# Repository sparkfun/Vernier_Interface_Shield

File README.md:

SparkFun Vernier Interface Shield Arduino Library
=================================================

[*SparkFun Vernier Interface Shield*](https://www.sparkfun.com/products/12858)

Repository Contents
-------------------

* **/src** - Source files for the library (.cpp, .h).
* **library.properties** - General library properties for the Arduino package manager. 
**Note**: For example sketches, please check the Vernier repository [here](https://github.com/VernierSoftwareTechnology/arduino).

Documentation
--------------
* **[Installing an Arduino Library Guide](https://learn.sparkfun.com/tutorials/installing-an-arduino-library)** - Basic information on how to install an Arduino library.
* **[Product Repository](https://github.com/sparkfun/Vernier_Interface_Shield)** - Main repository (including hardware files).
* **[Hookup Guide](https://learn.sparkfun.com/tutorials/vernier-shield-hookup-guide)** - Basic hookup guide for the SparkFun Vernier Interface Shield.

Products that use this Library 
---------------------------------

* [DEV-12858](https://www.sparkfun.com/products/12858)- SparkFun Vernier Interface Shield

License Information
-------------------

This product is _**open source**_! 

The **code** is beerware; if you see me (or any other SparkFun employee) at the local, and you've found our code helpful, please buy us a round!

Please use, reuse, and modify these files as you see fit. Please maintain attribution to SparkFun Electronics and release anything derivative under the same license.

Distributed as-is; no warranty is given.

- Your friends at SparkFun.

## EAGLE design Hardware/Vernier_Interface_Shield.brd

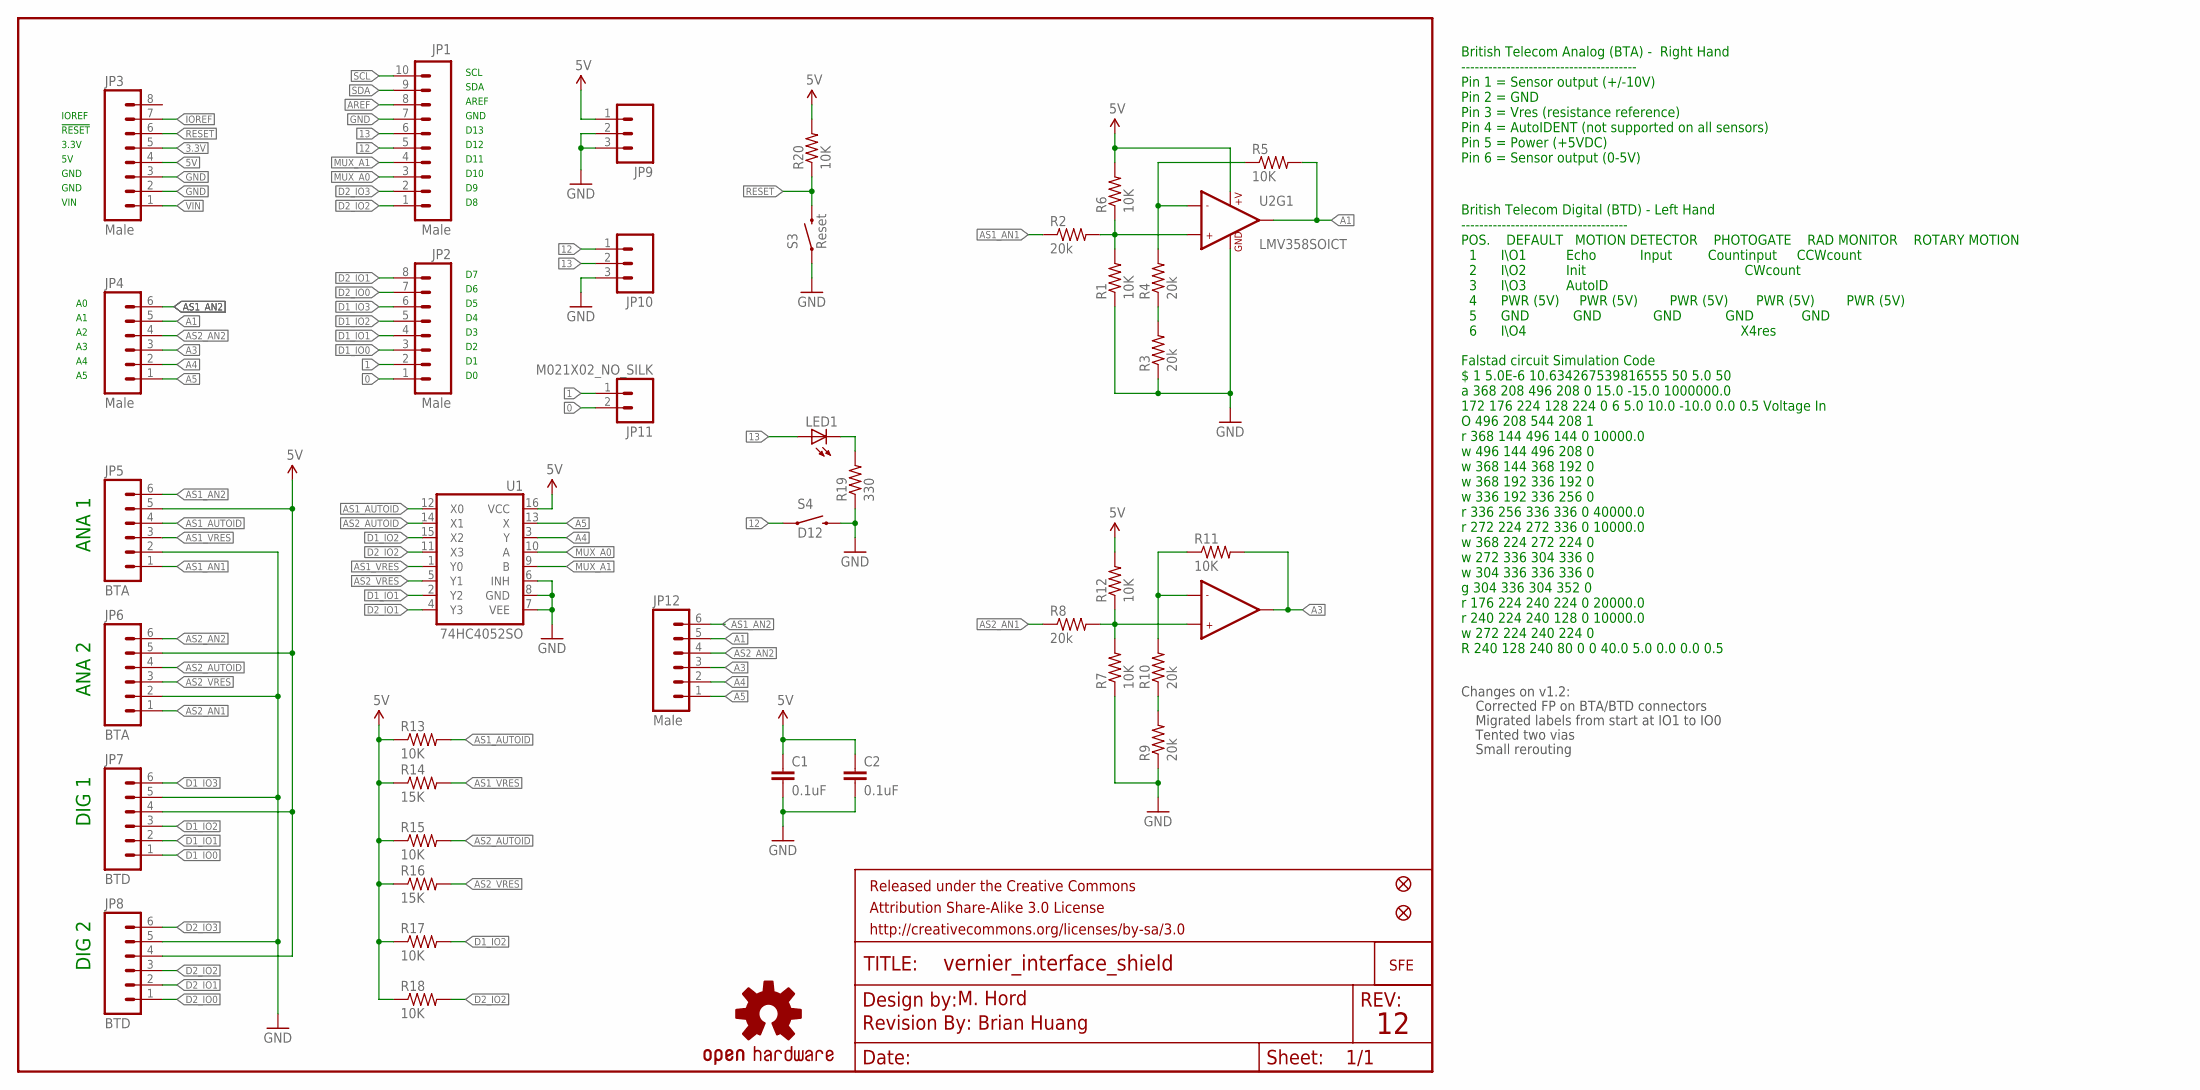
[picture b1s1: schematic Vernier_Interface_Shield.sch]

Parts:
C1, C2: 0.1uF; 0603-CAP
FID1, FID2: FIDUCIAL1X2; FIDUCIAL-1X2
FRAME1: FRAME-LETTER; CREATIVE_COMMONS
JP1: Male; 1X10_SMD_MALE
JP2, JP3: Male; 1X08_SMD_MALE
JP4: Male; 1X06_SMD_MALE
JP5, JP6: BTA
JP7, JP8: BTD
JP9, JP10: M031X03_NO_SILK; 1X03_NO_SILK
JP11: M021X02_NO_SILK; 1X02_NO_SILK
JP12: Male; 1X06
LED1: LED5MM
LOGO2: OSHW-LOGOS; OSHW-LOGO-S
LOGO_1: LOGO-SFESK; SFE-LOGO-FLAME
R1, R5, R6, R7, R11, R12, R13, R15, R17, R18, R20: 10K; 0603-RES
R2, R3, R4, R8, R9, R10: 20k; 0603-RES
R14, R16: 15K; 0603-RES
R19: 330; 0603-RES
S3: Reset; TACTILE-PTH
S4: D12; TACTILE-PTH
U1: 74HC4052SO; SO16
U2: LMV358SOICT; SO08-TIGHT
U$1: REVISION

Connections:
0: JP2.1, JP11.2
1: JP2.2, JP11.1
3.3V: JP3.5
5V: C1.1, C2.1, JP3.4, JP5.5, JP6.5, JP7.4, JP8.4, JP9.1, R6.2, R12.2, R13.1, R14.1, R15.1, R16.1, R17.1, R18.1, R20.2, U1.16 (VCC), U2.8 (+V)
12: JP1.5, JP10.1, S4.1
13: JP1.6, JP10.2, LED1.A
A1: JP4.5, JP12.5, R5.2, U2.1 (OUT1)
A3: JP4.3, JP12.3, R11.2, U2.7 (OUT2)
A4: JP4.2, JP12.2, U1.3 (Y)
A5: JP4.1, JP12.1, U1.13 (X)
AREF: JP1.8
AS1_AN1: JP5.1, R2.1
AS1_AN2: JP4.6, JP5.6, JP12.6
AS1_AUTOID: JP5.4, R13.2, U1.12 (X0)
AS1_VRES: JP5.3, R14.2, U1.1 (Y0)
AS2_AN1: JP6.1, R8.1
AS2_AN2: JP4.4, JP6.6, JP12.4
AS2_AUTOID: JP6.4, R15.2, U1.14 (X1)
AS2_VRES: JP6.3, R16.2, U1.5 (Y1)
D1_IO0: JP2.3, JP7.1
D1_IO1: JP2.4, JP7.2, U1.2 (Y2)
D1_IO2: JP2.5, JP7.3, R17.2, U1.15 (X2)
D1_IO3: JP2.6, JP7.6
D2_IO0: JP2.7, JP8.1
D2_IO1: JP2.8, JP8.2, U1.4 (Y3)
D2_IO2: JP1.1, JP8.3, R18.2, U1.11 (X3)
D2_IO3: JP1.2, JP8.6
GND: C1.2, C2.2, JP1.7, JP3.2, JP3.3, JP5.2, JP6.2, JP7.5, JP8.5, JP9.2, JP9.3, JP10.3, R1.1, R3.1, R7.1, R9.1, R19.1, S3.1, S4.3 (2), U1.6 (INH), U1.7 (VEE), U1.8 (GND), U2.4 (GND)
IOREF: JP3.7
MUX_A0: JP1.3, U1.10 (A)
MUX_A1: JP1.4, U1.9 (B)
unnamed: R1.2, R2.2, R6.1, U2.3 (+IN1)
unnamed: R3.2, R4.1
unnamed: R4.2, R5.1, U2.2 (-IN1)
unnamed: R9.2, R10.1
unnamed: R7.2, R8.2, R12.1, U2.5 (+IN2)
unnamed: R10.2, R11.1, U2.6 (-IN2)
unnamed: LED1.K (C), R19.2
RESET: JP3.6, R20.1, S3.3 (2)
SCL: JP1.10
SDA: JP1.9
VIN: JP3.1

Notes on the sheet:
SCL
SDA
AREF
GND
D13
D12
D11
D10
VIN
3.3V
!RESET
IOREF
ANA 1
ANA 2
DIG 1
DIG 2
M. Hord
British Telecom Analog (BTA) - Right Hand --------------------------------------- Pin 1 = Sensor output (+/-10V) Pin 2 = GND Pin 3 = Vres (resistance reference) Pin 4 = AutoIDENT (not supported on all sensors) Pin 5 = Power (+5VDC) Pin 6 = Sensor output (0-5V)
British Telecom Digital (BTD) - Left Hand ------------------------------------- POS. DEFAULT MOTION DETECTOR PHOTOGATE RAD MONITOR ROTARY MOTION 1 I\\O1 Echo Input Countinput CCWcount 2 I\\O2 Init CWcount 3 I\\O3 AutoID 4 PWR (5V) PWR (5V) PWR (5V) PWR (5V) PWR (5V) 5 GND GND GND GND GND 6 I\\O4 X4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
Falstad circuit Simulation Code $ 1 5.0E-6 10.634267539816555 50 5.0 50 a 368 208 496 208 0 15.0 -15.0 1000000.0 172 176 224 128 224 0 6 5.0 10.0 -10.0 0.0 0.5 Voltage In O 496 208 544 208 1 r 368 144 496 144 0 10000.0 w 496 144 496 208 0 w 368 144 368 192 0 w 368 192 336 192 0 w 336 192 336 256 0 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
Changes on v1.2:
Corrected FP on BTA/BTD connectors
Migrated labels from start at IO1 to IO0
Tented two vias
Small rerouting
Brian Huang

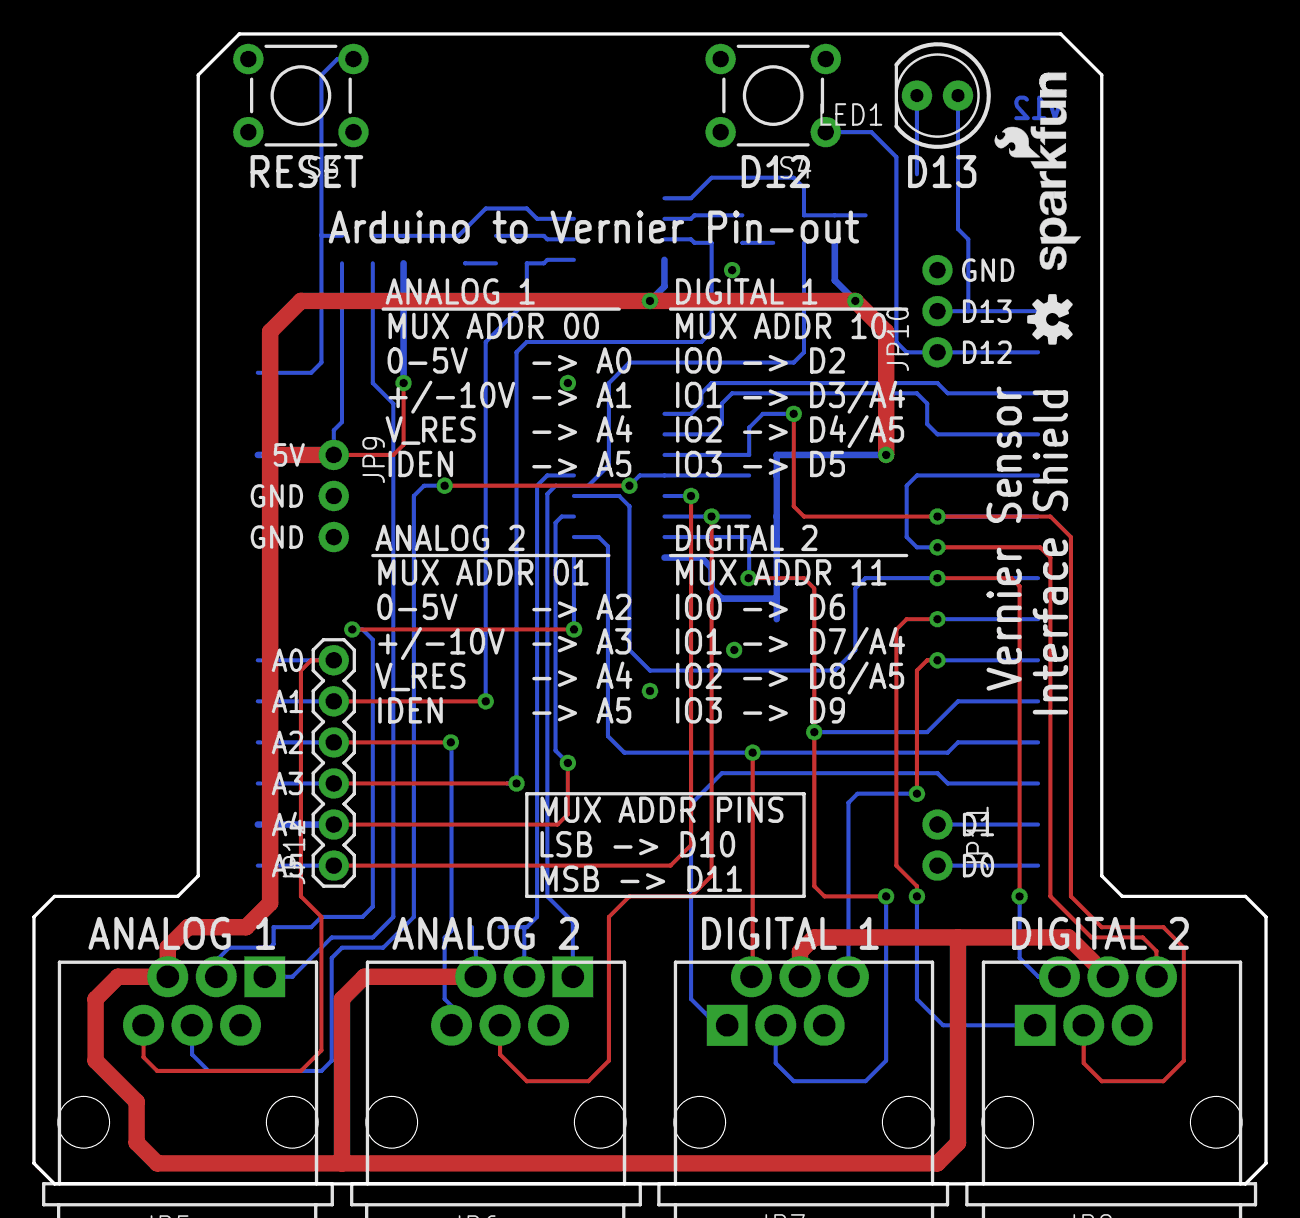
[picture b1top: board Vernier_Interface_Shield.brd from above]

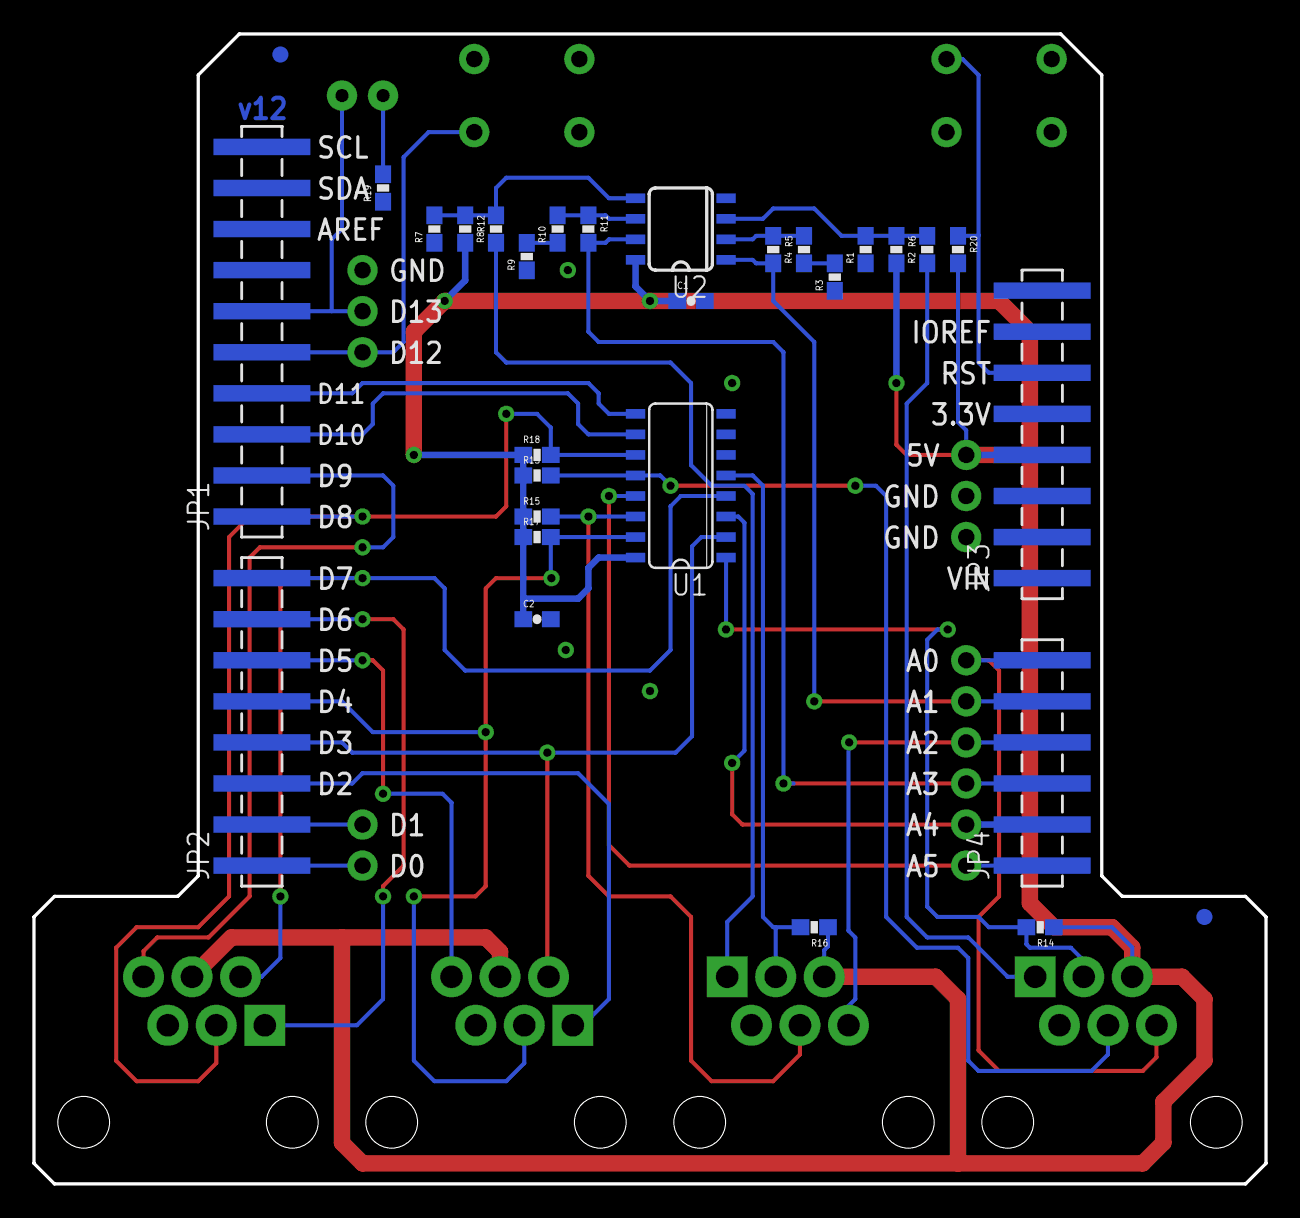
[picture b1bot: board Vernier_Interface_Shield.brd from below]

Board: 2 copper layers, 76.2 x 71.1 mm, 46 parts (30 on the bottom side), 36 nets.

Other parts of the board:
LOGO_3: LOGO-SFENW2; SFE-NEW-WEB

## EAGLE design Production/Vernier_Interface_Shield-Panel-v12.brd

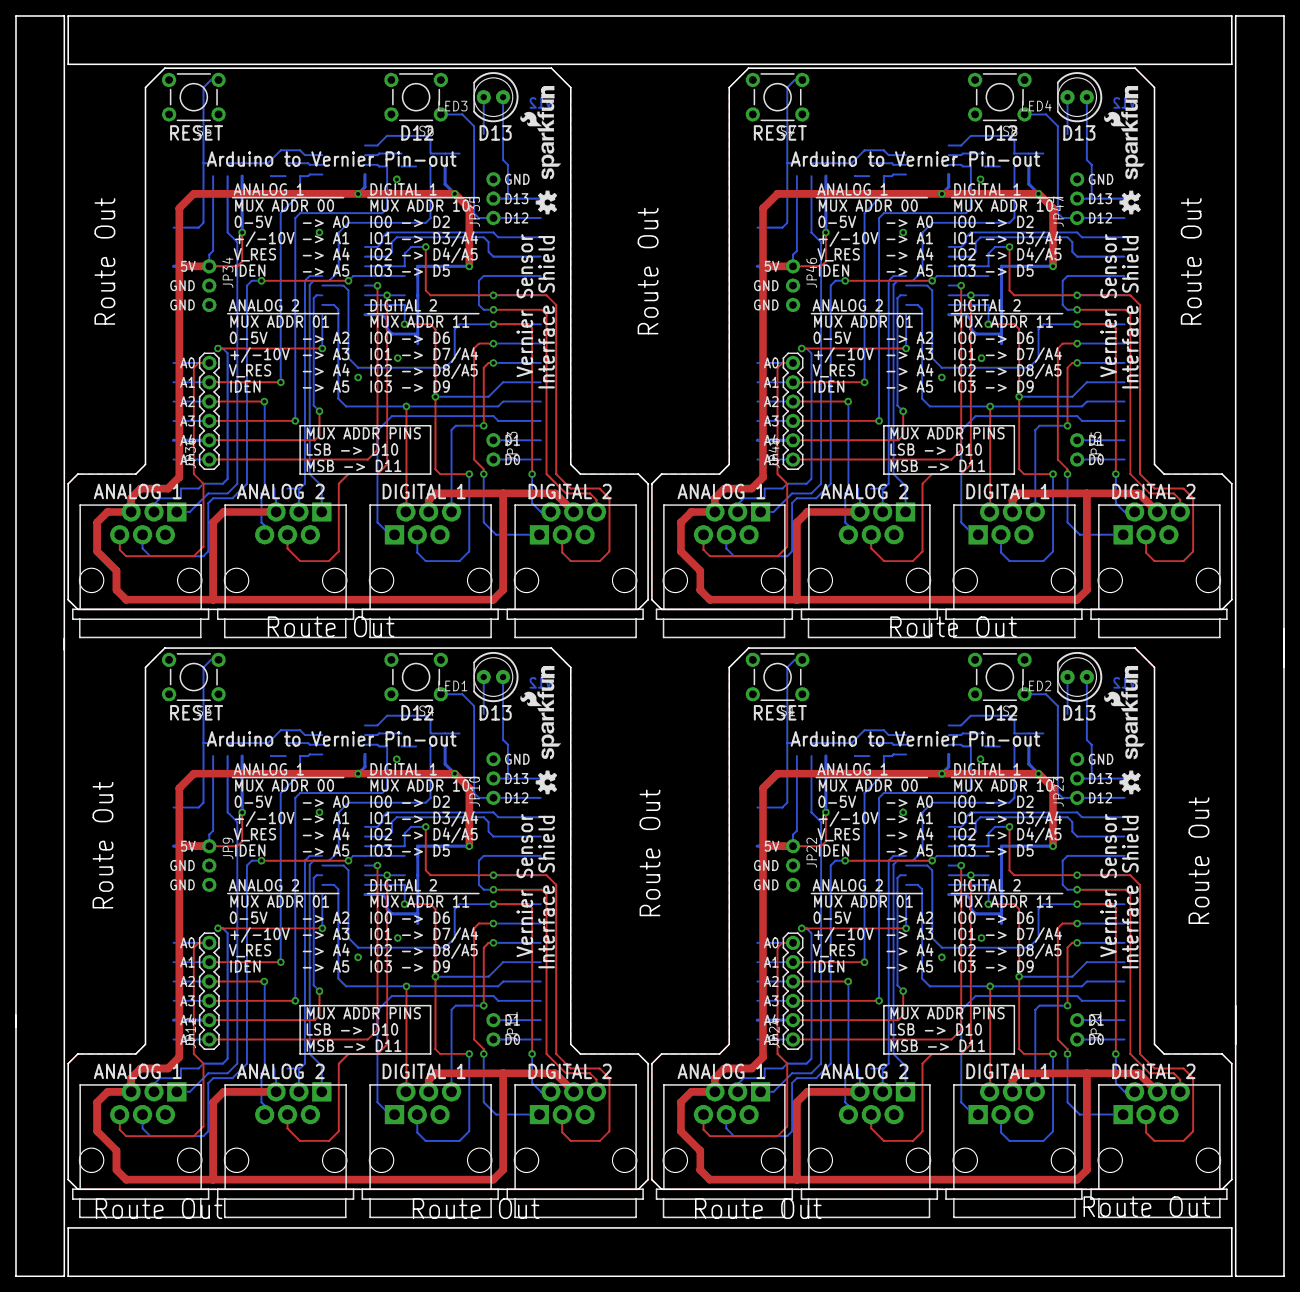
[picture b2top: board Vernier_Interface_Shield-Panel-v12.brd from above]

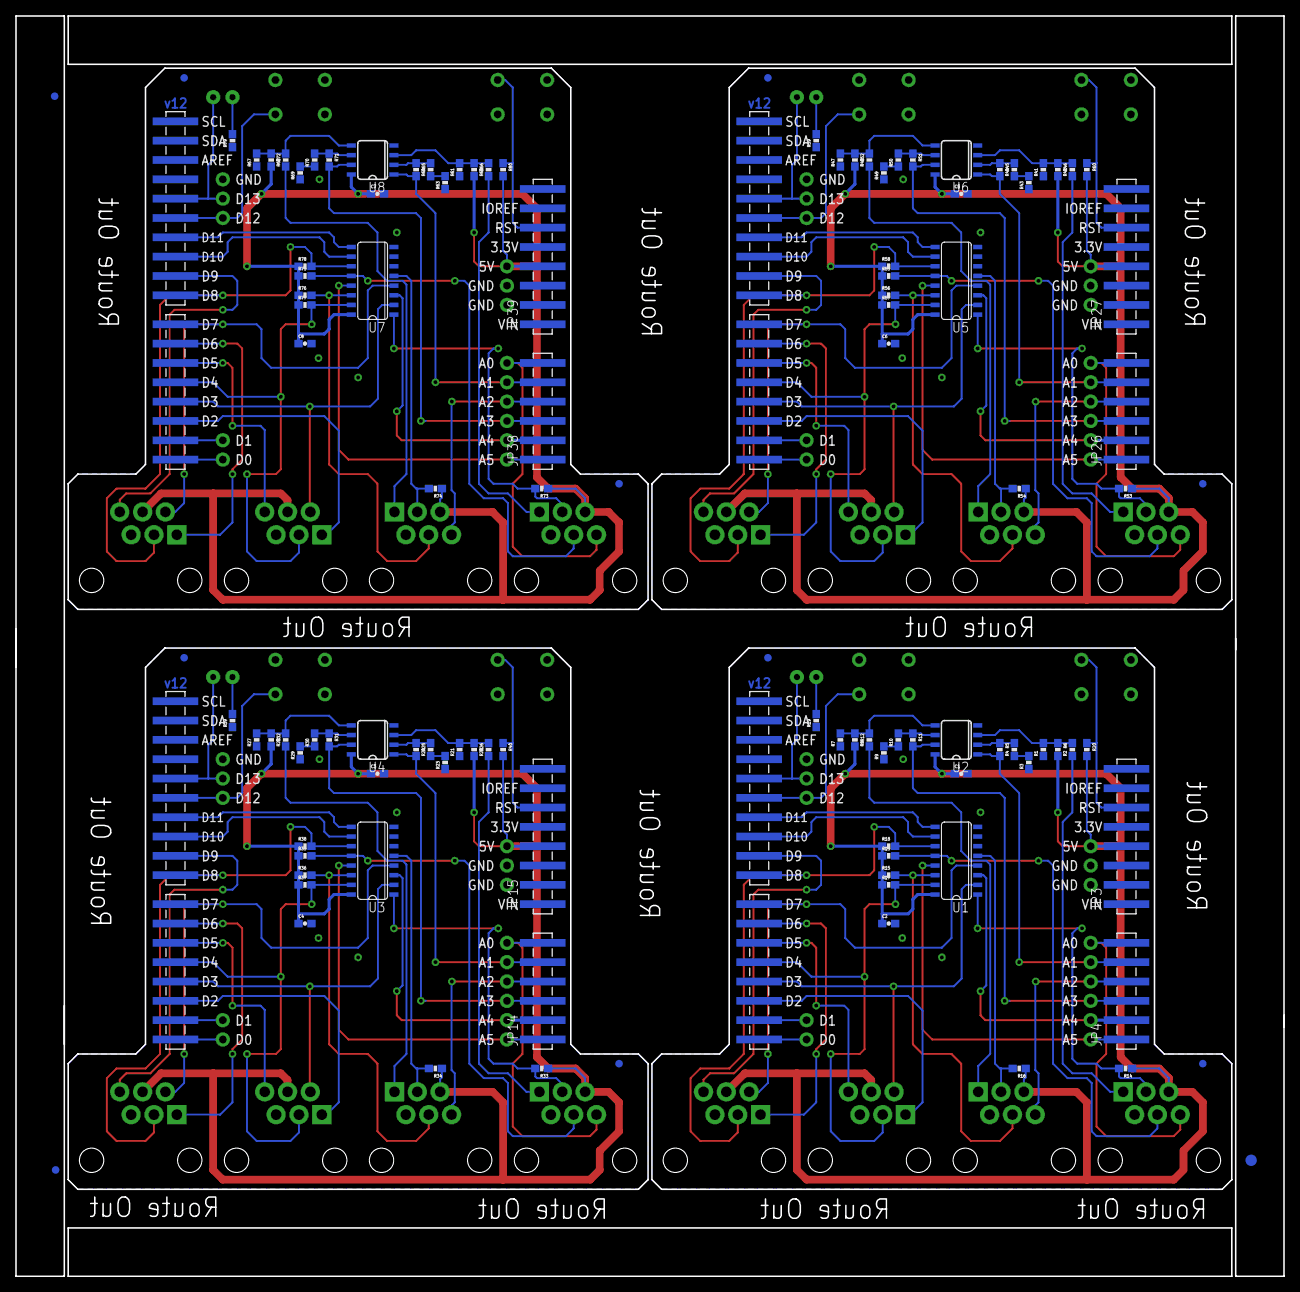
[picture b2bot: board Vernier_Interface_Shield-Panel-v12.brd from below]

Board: 2 copper layers, 166.6 x 165.6 mm, 179 parts (123 on the bottom side), 144 nets.

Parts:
C1, C2, C3, C4, C5, C6, C7, C8: 0.1uF; 0603-CAP
E$1: FIDUCIAL-1.5X3
E$4, E$6: FIDUCIAL-1X2
FID1, FID2, FID3, FID4, FID5, FID6, FID7, FID8: FIDUCIAL1X2; FIDUCIAL-1X2
JP1, JP13, JP25, JP37: Male; 1X10_SMD_MALE
JP2, JP3, JP15, JP16, JP27, JP28, JP39, JP40: Male; 1X08_SMD_MALE
JP4, JP14, JP26, JP38: Male; 1X06_SMD_MALE
JP5, JP6, JP18, JP19, JP30, JP31, JP42, JP43: BTA
JP7, JP8, JP17, JP20, JP29, JP32, JP41, JP44: BTD
JP9, JP10, JP22, JP23, JP34, JP35, JP46, JP47: 1X03_NO_SILK
JP11, JP21, JP33, JP45: M021X02_NO_SILK; 1X02_NO_SILK
JP12, JP24, JP36, JP48: Male; 1X06
LED1, LED2, LED3, LED4: LED5MM
LOGO1, LOGO2, LOGO3, LOGO4: OSHW-LOGOS; OSHW-LOGO-S
LOGO_1, LOGO_4, LOGO_6, LOGO_8: LOGO-SFESK; SFE-LOGO-FLAME
LOGO_2, LOGO_3, LOGO_5, LOGO_7: LOGO-SFENW2; SFE-NEW-WEB
R1, R5, R6, R7, R11, R12, R13, R15, R17, R18, R20, R21, R25, R26, R27, R31, R32, R35, R36, R37, R38, R40, R41, R45, R46, R47, R51, R52, R55, R56, R57, R58, R60, R61, R65, R66, R67, R71, R72, R75, R76, R77, R78, R80: 10K; 0603-RES
R2, R3, R4, R8, R9, R10, R22, R23, R24, R28, R29, R30, R42, R43, R44, R48, R49, R50, R62, R63, R64, R68, R69, R70: 20k; 0603-RES
R14, R16, R33, R34, R53, R54, R73, R74: 15K; 0603-RES
R19, R39, R59, R79: 330; 0603-RES
S1, S3, S5, S7: Reset; TACTILE-PTH
S2, S4, S6, S8: D12; TACTILE-PTH
U1, U3, U5, U7: 74HC4052SO; SO16
U2, U4, U6, U8: LMV358SOICT; SO08-TIGHT

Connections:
0: JP2.1, JP11.2
1: JP2.2, JP11.1
2: JP13.5, JP23.1, S2.1
3: JP16.1, JP21.2
4: JP16.2, JP21.1
5: JP13.6, JP23.2, LED2.A
5V: C1.1, C2.1, JP3.4, JP5.5, JP6.5, JP7.4, JP8.4, JP9.1, R6.2, R12.2, R13.1, R14.1, R15.1, R16.1, R17.1, R18.1, R20.2, U1.16, U2.8
5V1: C3.1, C4.1, JP15.4, JP17.4, JP18.5, JP19.5, JP20.4, JP22.1, R26.2, R32.2, R33.1, R34.1, R35.1, R36.1, R37.1, R38.1, R40.2, U3.16, U4.8
5V2: C5.1, C6.1, JP27.4, JP29.4, JP30.5, JP31.5, JP32.4, JP34.1, R46.2, R52.2, R53.1, R54.1, R55.1, R56.1, R57.1, R58.1, R60.2, U5.16, U6.8
5V3: C7.1, C8.1, JP39.4, JP41.4, JP42.5, JP43.5, JP44.4, JP46.1, R66.2, R72.2, R73.1, R74.1, R75.1, R76.1, R77.1, R78.1, R80.2, U7.16, U8.8
6: JP25.5, JP35.1, S6.1
7: JP28.1, JP33.2
8: JP28.2, JP33.1
9: JP25.6, JP35.2, LED3.A
10: JP37.5, JP47.1, S8.1
11: JP40.1, JP45.2
12: JP1.5, JP10.1, S4.1
13: JP1.6, JP10.2, LED1.A
14: JP40.2, JP45.1
15: JP37.6, JP47.2, LED4.A
A1: JP4.5, JP12.5, R5.2, U2.1
A2: JP14.2, JP24.2, U3.3
A3: JP4.3, JP12.3, R11.2, U2.7
A4: JP4.2, JP12.2, U1.3
A5: JP4.1, JP12.1, U1.13
A6: JP14.1, JP24.1, U3.13
A7: JP14.5, JP24.5, R25.2, U4.1
A8: JP14.3, JP24.3, R31.2, U4.7
A9: JP26.2, JP36.2, U5.3
A10: JP26.1, JP36.1, U5.13
A11: JP26.5, JP36.5, R45.2, U6.1
A12: JP26.3, JP36.3, R51.2, U6.7
A13: JP38.2, JP48.2, U7.3
A14: JP38.1, JP48.1, U7.13
A15: JP38.5, JP48.5, R65.2, U8.1
A16: JP38.3, JP48.3, R71.2, U8.7
AS1_AN1: JP5.1, R2.1
AS1_AN2: JP4.6, JP5.6, JP12.6
AS1_AN3: JP18.1, R22.1
AS1_AN4: JP14.6, JP18.6, JP24.6
AS1_AN5: JP30.1, R42.1
AS1_AN6: JP26.6, JP30.6, JP36.6
AS1_AN7: JP42.1, R62.1
AS1_AN8: JP38.6, JP42.6, JP48.6
AS1_AUTOID: JP5.4, R13.2, U1.12
AS1_AUTOID1: JP18.4, R35.2, U3.12
AS1_AUTOID2: JP30.4, R55.2, U5.12
AS1_AUTOID3: JP42.4, R75.2, U7.12
AS1_VRES: JP5.3, R14.2, U1.1
AS1_VRES1: JP18.3, R33.2, U3.1
AS1_VRES2: JP30.3, R53.2, U5.1
AS1_VRES3: JP42.3, R73.2, U7.1
AS2_AN1: JP6.1, R8.1
AS2_AN2: JP4.4, JP6.6, JP12.4
AS2_AN3: JP14.4, JP19.6, JP24.4
AS2_AN4: JP19.1, R28.1
AS2_AN5: JP26.4, JP31.6, JP36.4
AS2_AN6: JP31.1, R48.1
AS2_AN7: JP38.4, JP43.6, JP48.4
AS2_AN8: JP43.1, R68.1
AS2_AUTOID: JP6.4, R15.2, U1.14
AS2_AUTOID1: JP19.4, R36.2, U3.14
AS2_AUTOID2: JP31.4, R56.2, U5.14
AS2_AUTOID3: JP43.4, R76.2, U7.14
AS2_VRES: JP6.3, R16.2, U1.5
AS2_VRES1: JP19.3, R34.2, U3.5
AS2_VRES2: JP31.3, R54.2, U5.5
AS2_VRES3: JP43.3, R74.2, U7.5
D1_IO0: JP2.3, JP7.1
D1_IO1: JP2.4, JP7.2, U1.2
D1_IO2: JP2.5, JP7.3, R17.2, U1.15
D1_IO3: JP2.6, JP7.6
D1_IO4: JP16.6, JP17.6
D1_IO5: JP16.5, JP17.3, R37.2, U3.15
D1_IO6: JP16.4, JP17.2, U3.2
D1_IO7: JP16.3, JP17.1
D1_IO8: JP28.6, JP29.6
D1_IO9: JP28.5, JP29.3, R57.2, U5.15
D1_IO10: JP28.4, JP29.2, U5.2
D1_IO11: JP28.3, JP29.1
D1_IO12: JP40.6, JP41.6
D1_IO13: JP40.5, JP41.3, R77.2, U7.15
D1_IO14: JP40.4, JP41.2, U7.2
D1_IO15: JP40.3, JP41.1
D2_IO0: JP2.7, JP8.1
D2_IO1: JP2.8, JP8.2, U1.4
D2_IO2: JP1.1, JP8.3, R18.2, U1.11
D2_IO3: JP1.2, JP8.6
D2_IO4: JP13.2, JP20.6
D2_IO5: JP13.1, JP20.3, R38.2, U3.11
D2_IO6: JP16.8, JP20.2, U3.4
D2_IO7: JP16.7, JP20.1
D2_IO8: JP25.2, JP32.6
D2_IO9: JP25.1, JP32.3, R58.2, U5.11
D2_IO10: JP28.8, JP32.2, U5.4
D2_IO11: JP28.7, JP32.1
D2_IO12: JP37.2, JP44.6
D2_IO13: JP37.1, JP44.3, R78.2, U7.11
D2_IO14: JP40.8, JP44.2, U7.4
D2_IO15: JP40.7, JP44.1
GND: C1.2, C2.2, JP1.7, JP3.2, JP3.3, JP5.2, JP6.2, JP7.5, JP8.5, JP9.2, JP9.3, JP10.3, R1.1, R3.1, R7.1, R9.1, R19.1, S3.1, S4.3, U1.6, U1.7, U1.8, U2.4
GND1: C3.2, C4.2, JP13.7, JP15.2, JP15.3, JP17.5, JP18.2, JP19.2, JP20.5, JP22.2, JP22.3, JP23.3, R21.1, R23.1, R27.1, R29.1, R39.1, S1.1, S2.3, U3.6, U3.7, U3.8, U4.4
GND2: C5.2, C6.2, JP25.7, JP27.2, JP27.3, JP29.5, JP30.2, JP31.2, JP32.5, JP34.2, JP34.3, JP35.3, R41.1, R43.1, R47.1, R49.1, R59.1, S5.1, S6.3, U5.6, U5.7, U5.8, U6.4
GND3: C7.2, C8.2, JP37.7, JP39.2, JP39.3, JP41.5, JP42.2, JP43.2, JP44.5, JP46.2, JP46.3, JP47.3, R61.1, R63.1, R67.1, R69.1, R79.1, S7.1, S8.3, U7.6, U7.7, U7.8, U8.4
MUX_A0: JP1.3, U1.10
MUX_A1: JP1.4, U1.9
MUX_A2: JP13.3, U3.10
MUX_A3: JP13.4, U3.9
MUX_A4: JP25.3, U5.10
MUX_A5: JP25.4, U5.9
MUX_A6: JP37.3, U7.10
MUX_A7: JP37.4, U7.9
unnamed: R1.2, R2.2, R6.1, U2.3
unnamed: R3.2, R4.1
unnamed: R4.2, R5.1, U2.2
unnamed: R23.2, R24.1
unnamed: R9.2, R10.1
unnamed: R7.2, R8.2, R12.1, U2.5
unnamed: R10.2, R11.1, U2.6
unnamed: LED1.K, R19.2
unnamed: R21.2, R22.2, R26.1, U4.3
unnamed: R24.2, R25.1, U4.2
unnamed: R29.2, R30.1
unnamed: R27.2, R28.2, R32.1, U4.5
unnamed: R30.2, R31.1, U4.6
unnamed: LED2.K, R39.2
unnamed: R43.2, R44.1
unnamed: R41.2, R42.2, R46.1, U6.3
unnamed: R44.2, R45.1, U6.2
unnamed: R49.2, R50.1
unnamed: R47.2, R48.2, R52.1, U6.5
unnamed: R50.2, R51.1, U6.6
unnamed: LED3.K, R59.2
unnamed: R63.2, R64.1
unnamed: R61.2, R62.2, R66.1, U8.3
unnamed: R64.2, R65.1, U8.2
unnamed: R69.2, R70.1
unnamed: R67.2, R68.2, R72.1, U8.5
unnamed: R70.2, R71.1, U8.6
unnamed: LED4.K, R79.2
RESET: JP3.6, R20.1, S3.3
RESET1: JP15.6, R40.1, S1.3
RESET2: JP27.6, R60.1, S5.3
RESET3: JP39.6, R80.1, S7.3

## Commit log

2013-06-10 Ready for protos
2013-08-15 Tweaks towards v02
2013-08-22 Updated footprints of BTA and BTD
    Fixed the footprints of BTA and BTD.
    Corrected the BTD pin numbering.
    Rotated the design so that the connectors don't short out on the USB
    cage.
    V03
2013-08-23 Fixed traces, ran DRC, etc...
    Updated traces, fixed errors in DRC... more tweaks toward v02
2013-08-26 addtl clean-up: corrected resistor spacing
    Corrected resistor spacing and cleaned-up resulting traces.
2013-08-27 Updated footprints of BTA and BTD connectors
2013-08-27 Ready for protos!
    Everything's ready to go! No changes to the BOM. Can we order 4 protos
    this time?
2013-08-28 One last update for v02 - updated bottom silk
    Updated bottom silk for where VIAS are interfering with the pin labels.
2013-09-21 Changed Pins 2 and 3 to BTD connector 1
    Changed circuit so that Pins 2 and 3 are connected to BTD 1 - allows for
    use of Hardware interrupts from Arduino.
    Also cleaned up silks
2013-09-23 Changed pins one last time...
    Changed Digital Pins so that it's pins 2, 3, 4, 5 on Dig 1 and 6, 7, 8
    ,9 on Dig 2
2013-09-23 Updated revision code - ready for protos
    Hopefully the last round of protos for this board. - Updated silks,
    moved VIAS so as not to interfere with printing.
2013-10-22 Switched Digital 1 and Digital 2 on the Board
    Fixed the Digital 1 and Digital 2. V03 had the two connectors flipped.
2013-10-28 Adjusted silk on digital header list
2013-10-31 Initial start of Vernier Library routines
2013-11-14 Release version
2013-11-14 Added micro Fiducial to board
2013-11-14 Created Panel
2013-11-14 Added "Route Out" for GP routing
2013-12-09 Put on grid, rm weird stop on back, to v11
2013-12-09 Move borders to 50th grid lines
2013-12-09 Re-created Panel v11
2013-12-09 added route out for GP
2013-12-12 Move board outline from tDocu to Dimension
2013-12-13 Re-re-created Panel v11
2014-01-18 Updated connector FPs. Tented some vias. Removed extra silk.
    The A5 to A0 labels were of different size and didn't see to go
    anywhere. Removed them.
2014-01-18 Shrunk board. Updated version number to 1.2.
2014-01-18 Touched up schematic. Updated version number.
    Pushed some schematic components onto grid. Replaced button symbols with
    single action symbol.
2014-01-18 Small component/silk overlap fix.
2014-01-30 Repo clean up and README update
2014-01-30 Update README.md
    Changing product description.
2014-02-06 Changed silk to fix bug #4
    Changed silk to start at IO0 instead of IO1. This is per Vernier's
    request.
2014-04-21 Updated A0-A5 vias to be exposed to allow for probe pins
    Swapped out 6 vias on A0 to A5 with M06 for exposed copper vias to allow
    for probe points
2014-07-23 Updated the Top layer Silk
    Updated top layer silk to have A0-A5 next to the exposed vias. Moved the
    exposed vias for 5V and GND to line up with A0-A5.
2014-07-23 Deleted extra files
    Removed the extra vernier_interface_shield2.xxx files
2014-07-23 Silk update
    Found two text labels A4 / A5 that weren't lined up. Fixed.
2014-08-04 Fixing layout of license and adding revision by info
2014-08-08 removed micro fids, added regular
2014-08-08 created panel v12
2014-09-03 re-created panel v12 with proper spacing
2015-01-02 Updating README with new product links
2015-04-24 Squashed 'Libraries/Arduino/' content from commit 605cf21
    git-subtree-dir: Libraries/Arduino
    git-subtree-split: 605cf21e6fa902c52472fac919dcde89b24b8e8a
2015-04-24 Changed library to new subtree.
2015-05-14 Updating README, fixing naming conventions
2015-05-14 Squashed 'Libraries/Arduino/' changes from 605cf21..4488417
    git-subtree-dir: Libraries/Arduino
    git-subtree-split: 44884171363cd44c3c6dfda6376193d3172a4ff1

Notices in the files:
parts and their libraries:
SparkFun-Aesthetics: Licensing: CC v3.0 Share-Alike You are welcome to use this library for commercial purposes.
SparkFun-Aesthetics: Released under the Creative Commons Attribution Share-Alike 3.0 License
SparkFun-Aesthetics: http://creativecommons.org/licenses/by-sa/3.0
